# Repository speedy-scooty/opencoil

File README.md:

# Opencoil

Goodies to produce your own e-scooter add-ons.

* CNC: an outline to cnc/lasercut to mount various hardware to charging pads
* Code: example code + instructions
* Coil: what coils do you need to harness the power of wireless energy in the wild?
* Electronics: schematics, kicad files to make your own pcb + wiring instructions
* Mold: a 3d model of the actual charging pad, to thermoform your own replicas.

https://opencoil.show/

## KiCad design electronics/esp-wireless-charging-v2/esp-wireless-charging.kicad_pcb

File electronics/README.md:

# opencoil / electronics

*Assembled pcb v1*

As of 2022 there is a PCB version 2 with extra breakout gpio pins, schematic [here](https://github.com/speedy-scooty/opencoil/blob/b7b5a5852f1626367fa80c27c357b1f2ee417245/electronics/esp-wireless-charging-v2/esp-wireless-charging.pdf)

*Assembled pcb v2*

### Bill of Materials 

* PCB: Send the gerbers from this repo to your fab of choice.
* ESP12F: Widely available.
* AM1117 3.3v Regulator: Widely available.
* QI compatible wireless charging coil delivering 5v and > [500 mA](https://docs.ai-thinker.com/_media/esp8266/docs/esp-12f_product_specification_en.pdf): For example [this](https://aliexpress.com/item/4001154059743.html), search keywords: "pcba receiver module qi". Alternatively you could repurpose 'adaptor coils' advertised to convert non-QI phones to wireless charging, such as [these](https://www.pearl.de/mtrkw-9811-qi-kompatible-receiver-pads.shtml)*. 

**NOTE**: Be aware that these 'adaptor coils' could contain additional circuitry that condition the output for use with specific mobile phones (the pearl.de ones do). [Here](https://github.com/speedy-scooty/opencoil/tree/main/coil) is a guide how to modify the 'pearl' coils to deliver maximum voltage (5v)constantly, instead of switching to low power, 2.5v output when not enough/too much current is drawn.

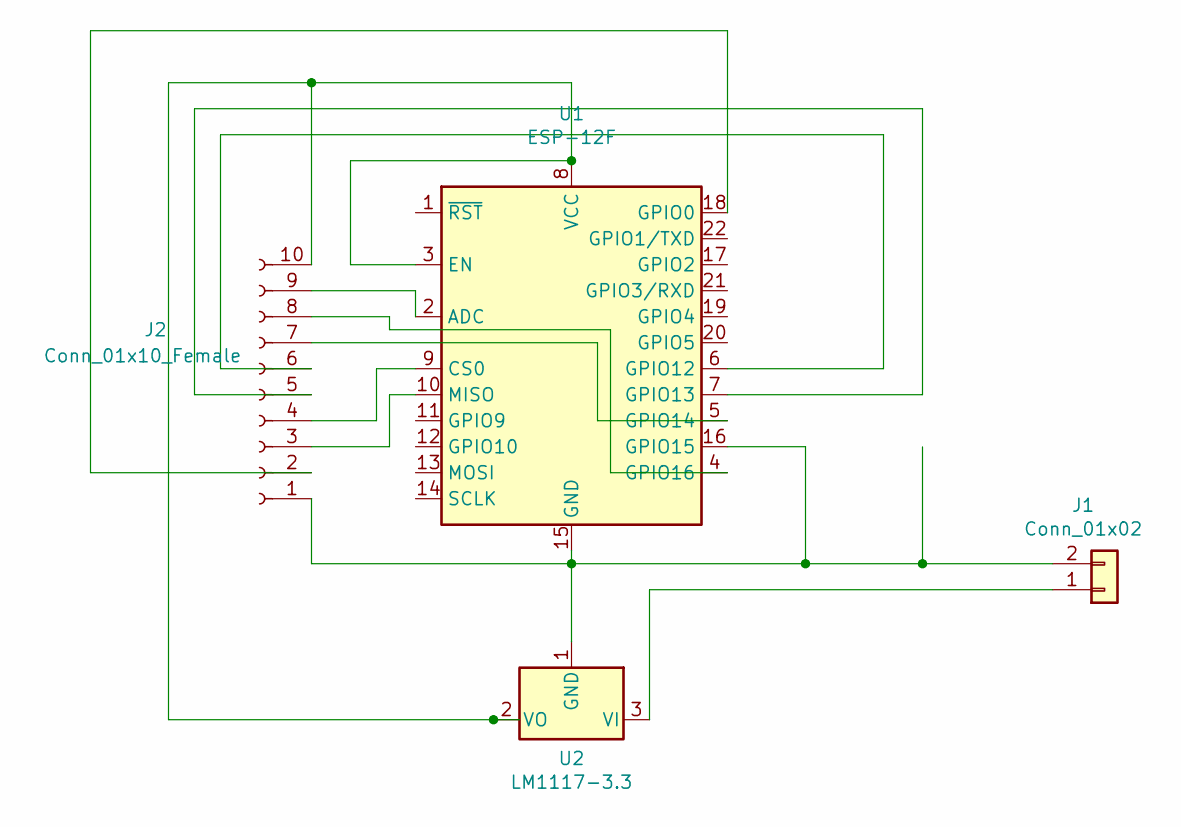
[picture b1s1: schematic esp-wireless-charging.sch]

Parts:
J1: Conn_01x02; PinHeader_1x02_P2.54mm_Vertical
J2: Conn_01x10_Female; PinHeader_1x10_P2.54mm_Vertical
U1: ESP-12F; ESP-12E
U2: LM1117-3.3; SOT-223-3_TabPin2

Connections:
unnamed: J1.1, U2.3 (VI)
unnamed: J1.2, J2.1, U1.15 (GND), U1.16 (GPIO15), U2.1 (GND)
unnamed: J2.2, U1.18 (GPIO0)
unnamed: J2.3, U1.10 (MISO)
unnamed: J2.4, U1.9 (CS0)
unnamed: J2.5, U1.7 (GPIO13)
unnamed: J2.6, U1.6 (GPIO12)
unnamed: J2.7, U1.5 (GPIO14)
unnamed: J2.8, U1.4 (GPIO16)
unnamed: J2.9, U1.2 (ADC)
unnamed: J2.10, U1.3 (EN), U1.8 (VCC), U2.2 (VO)

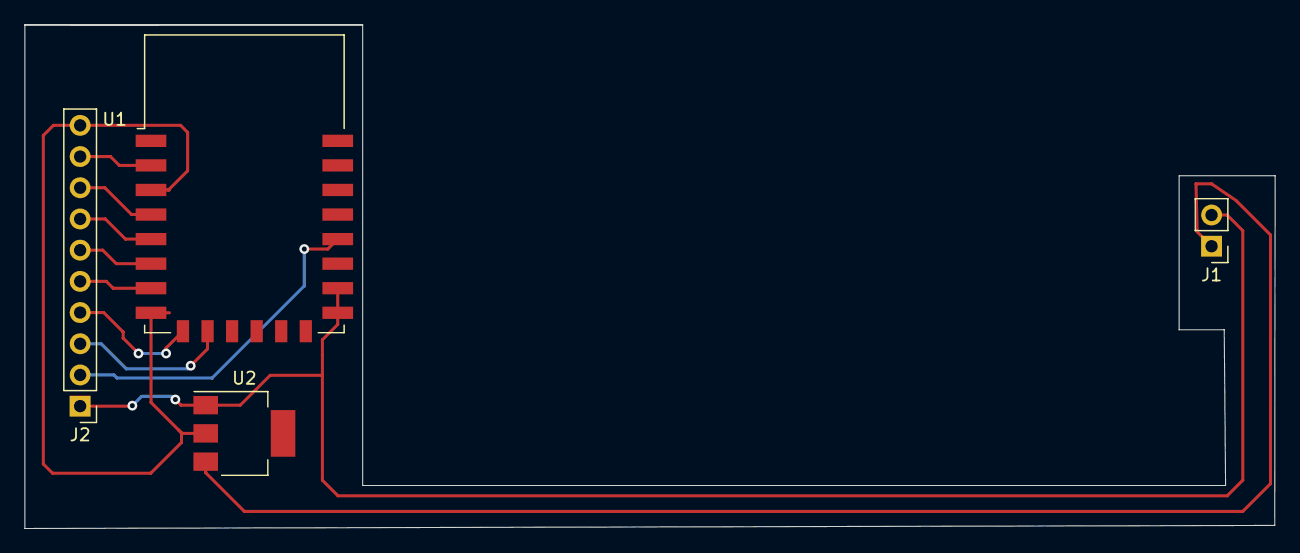
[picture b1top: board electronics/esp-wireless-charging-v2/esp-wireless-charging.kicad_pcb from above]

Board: 2 copper layers, 101.8 x 41.0 mm, 4 parts (0 on the bottom side), 11 nets.

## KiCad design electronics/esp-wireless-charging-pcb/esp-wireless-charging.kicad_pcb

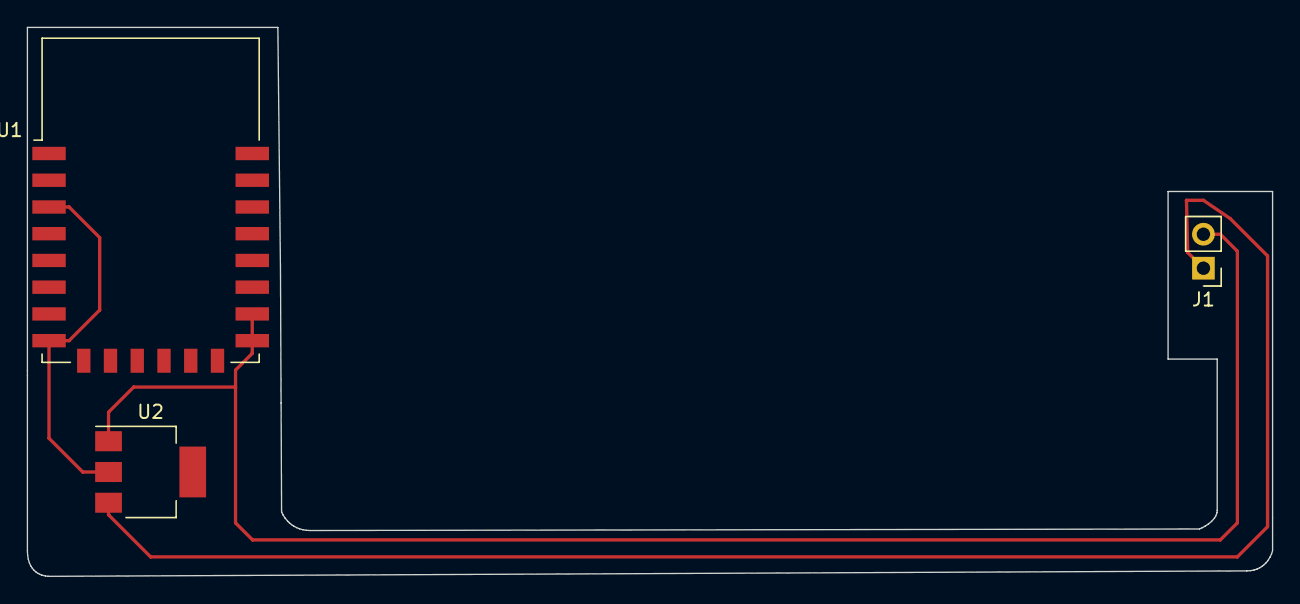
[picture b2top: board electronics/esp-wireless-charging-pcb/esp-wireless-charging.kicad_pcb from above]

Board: 2 copper layers, 93.1 x 41.1 mm, 4 parts (0 on the bottom side), 3 nets.

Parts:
J1: Conn_01x02; PinHeader_1x02_P2.54mm_Vertical
Ref**: Val**; drawing
U1: ESP-12F; ESP-12E
U2: LM1117-3.3; SOT-223-3_TabPin2

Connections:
unnamed: J1.1, U2.3
unnamed: J1.2, U1.15, U1.16, U2.1
unnamed: U1.3, U1.8, U2.2

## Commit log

2020-12-29 added images and notes
2020-12-29 added project url
2022-09-10 3D printable mold
    This is a 3d printable version of the TIER charging pad to create vacuum molds with
2022-09-10 Code
    this is the code to flash your ESP8266 to create a opencoil popup portal to display your works in
2022-09-10 added custom electronics schematics, pcb
2022-09-10 adding latest pcb and schematic
2022-11-23 added Scooter_Revolution sketch
    mod of the original coil with a speaker to play an mp3 onces the adsapter is powered
